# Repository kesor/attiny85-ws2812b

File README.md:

# attiny85-ws2812b
Narrow PCB attiny85 ws2812b led driver

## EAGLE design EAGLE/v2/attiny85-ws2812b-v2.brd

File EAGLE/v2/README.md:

# ATtiny85 WS2812B v2

## Layers

#### Top

#### Bottom

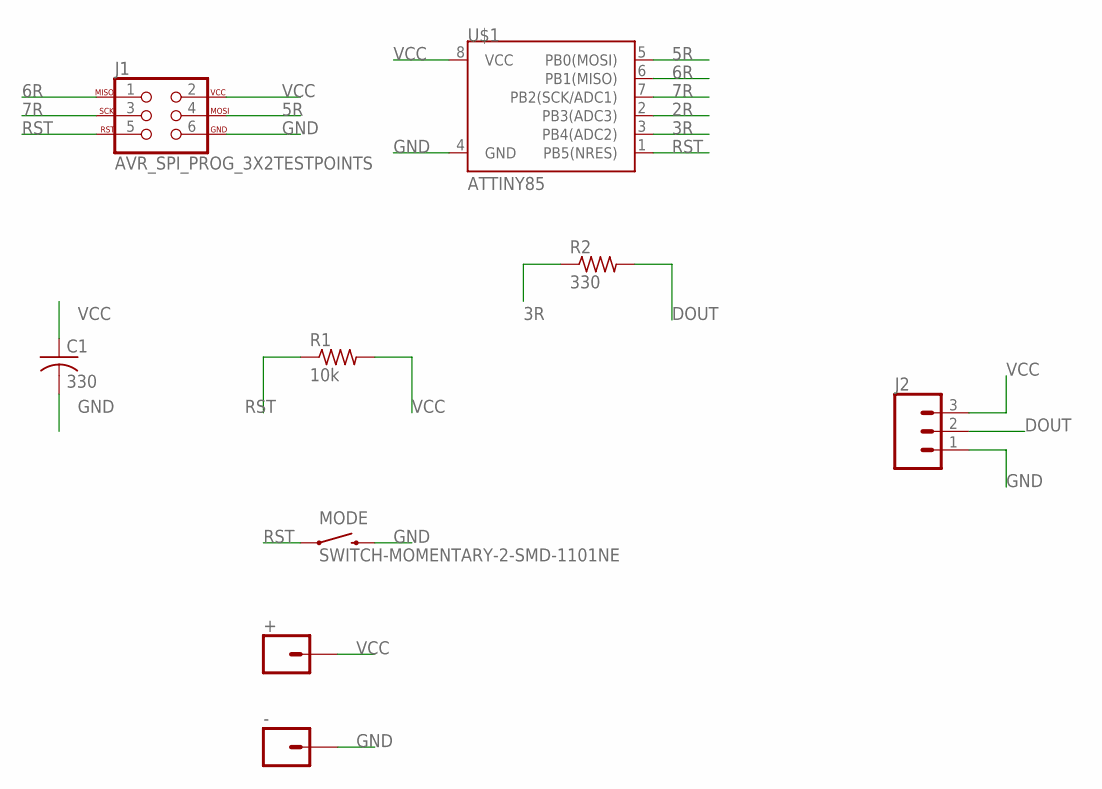
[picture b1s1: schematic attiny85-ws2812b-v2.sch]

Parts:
+: CONN_01PTH_NO_SILK_YES_STOP; 1X01_NO_SILK
-: CONN_01PTH_NO_SILK_YES_STOP; 1X01_NO_SILK
C1: 330; C0603
J1: AVR_SPI_PROG_3X2TESTPOINTS; 2X3_TEST_POINTS
J2: CONN_031X03_NO_SILK; 1X03_NO_SILK
MODE: SWITCH-MOMENTARY-2-SMD-1101NE; TACTILE-SWITCH-1101NE
R1: 10k; R0603
R2: 330; R0603
U$1: ATTINY85; SO08-EIAJ

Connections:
2R: U$1.2 (PB3(ADC3))
3R: R2.1, U$1.3 (PB4(ADC2))
5R: J1.4, U$1.5 (PB0(MOSI))
6R: J1.1, U$1.6 (PB1(MISO))
7R: J1.3, U$1.7 (PB2(SCK/ADC1))
DOUT: J2.2, R2.2
GND: -.1, C1.2, J1.6, J2.1, MODE.P$2 (2), U$1.4 (GND)
RST: J1.5, MODE.P$1 (1), R1.1, U$1.1 (PB5(NRES))
VCC: +.1, C1.1, J1.2, J2.3, R1.2, U$1.8 (VCC)

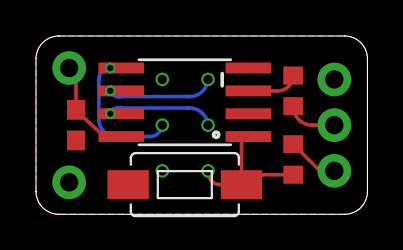
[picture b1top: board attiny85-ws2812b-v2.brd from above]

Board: 2 copper layers, 18.4 x 9.9 mm, 9 parts (1 on the bottom side), 8 nets.

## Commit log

2018-03-07 add the first version of attiny85-ws2812b driver
2018-03-07 add images for top and bottom
2018-03-07 add comment about shared oshpark project
2018-03-07 embed images into readme for v1
2018-03-07 descriptive readme
2018-03-07 typo in title
2018-06-06 add a smaller v2 version
2018-06-06 fix README.md image links
2018-06-06 fix typo in readme

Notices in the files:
parts and their libraries:
SparkFun: Licensing: CC v3.0 Share-Alike You are welcome to use this library for commercial purposes.
